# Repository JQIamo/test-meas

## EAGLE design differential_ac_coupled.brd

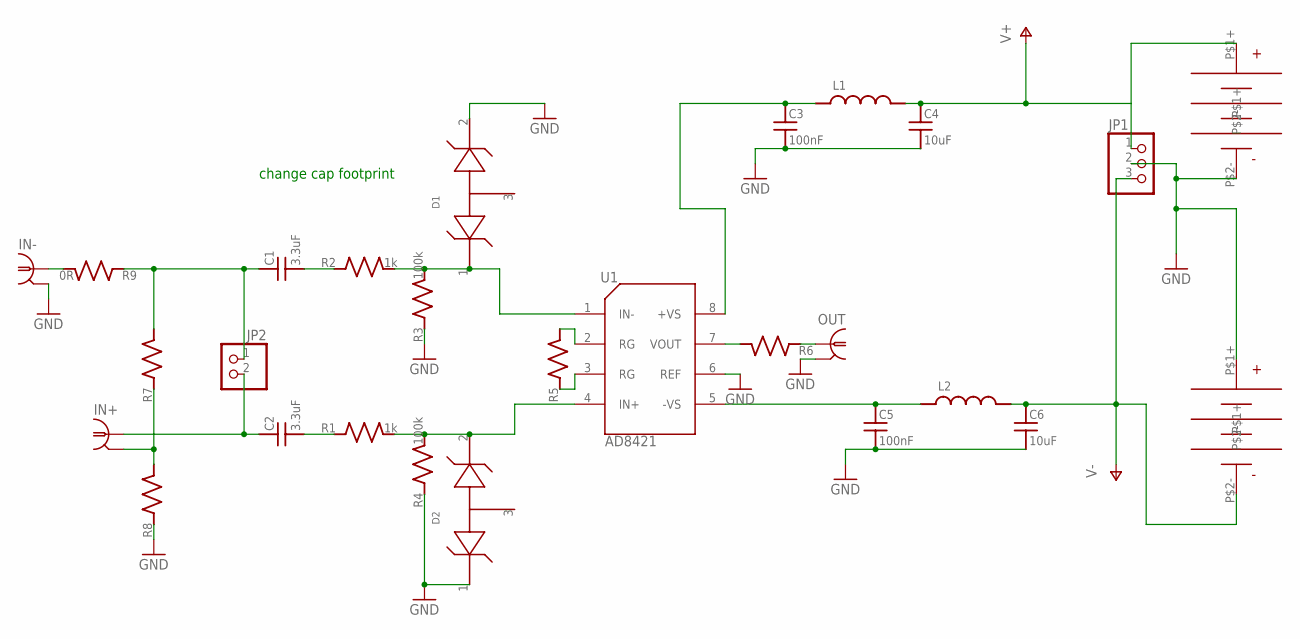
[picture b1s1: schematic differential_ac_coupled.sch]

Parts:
C1, C2: 3.3uF; CKG-JLEAD
C3, C5: 100nF; C_MLCC_0603
C4, C6: 10uF; C_MLCC_0805
D1, D2: ZENER-DUAL; SOT-23
IN+: BNC-H; BNC90
IN-: BNC-H; BNC90
JP1: PINHD-1X3; 1X03
JP2: SCRWTRM-1X2/90_ED550; 1X02_RA_SCRWTRM_ED550
L1, L2: L_FERRITE_SMDLFERRITE_0603; L_FERRITE_0603
OUT: BNC-H; BNC90
R1, R2: 1k; R_1206
R3, R4: 100k; R_1206
R5, R6: R_SMDR0603; R_0603
R7, R8: R_SMDR1206; R_1206
R9: 0R; R_1206
U1: AD8421; SOIC-8
U$1, U$2: BATT-HOLDER; BH23A-BATT-HOLDER

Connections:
GND: C3.P$2 (2), C4.P$2 (2), C5.P$2 (2), C6.P$2 (2), D1.2, D2.1, IN-.2, JP1.2, OUT.2, R3.P$1 (1), R4.P$1 (1), R8.P$1 (1), U1.6 (REF), U$1.P$2-, U$2.P$1+
unnamed: C1.P$2 (2), R2.P$1 (1)
unnamed: C2.P$2 (2), R1.P$1 (1)
unnamed: D2.2, R1.P$2 (2), R4.P$2 (2), U1.4 (IN+)
unnamed: D1.1, R2.P$2 (2), R3.P$2 (2), U1.1 (IN-)
unnamed: OUT.1, R6.P$1 (1)
unnamed: C3.P$1 (1), L1.P$1 (1), U1.8 (+VS)
unnamed: R5.P$2 (2), U1.2 (RG)
unnamed: R5.P$1 (1), U1.3 (RG)
unnamed: C5.P$1 (1), L2.P$1 (1), U1.5 (-VS)
unnamed: R6.P$2 (2), U1.7 (VOUT)
unnamed: C2.P$1 (1), IN+.1, JP2.2
unnamed: C1.P$1 (1), JP2.1, R7.P$2 (2), R9.P$1 (1)
unnamed: IN-.1, R9.P$2 (2)
unnamed: IN+.2, R7.P$1 (1), R8.P$2 (2)
V+: C4.P$1 (1), JP1.1, L1.P$2 (2), U$1.P$1+
V-: C6.P$1 (1), JP1.3, L2.P$2 (2), U$2.P$2-

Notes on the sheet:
change cap footprint

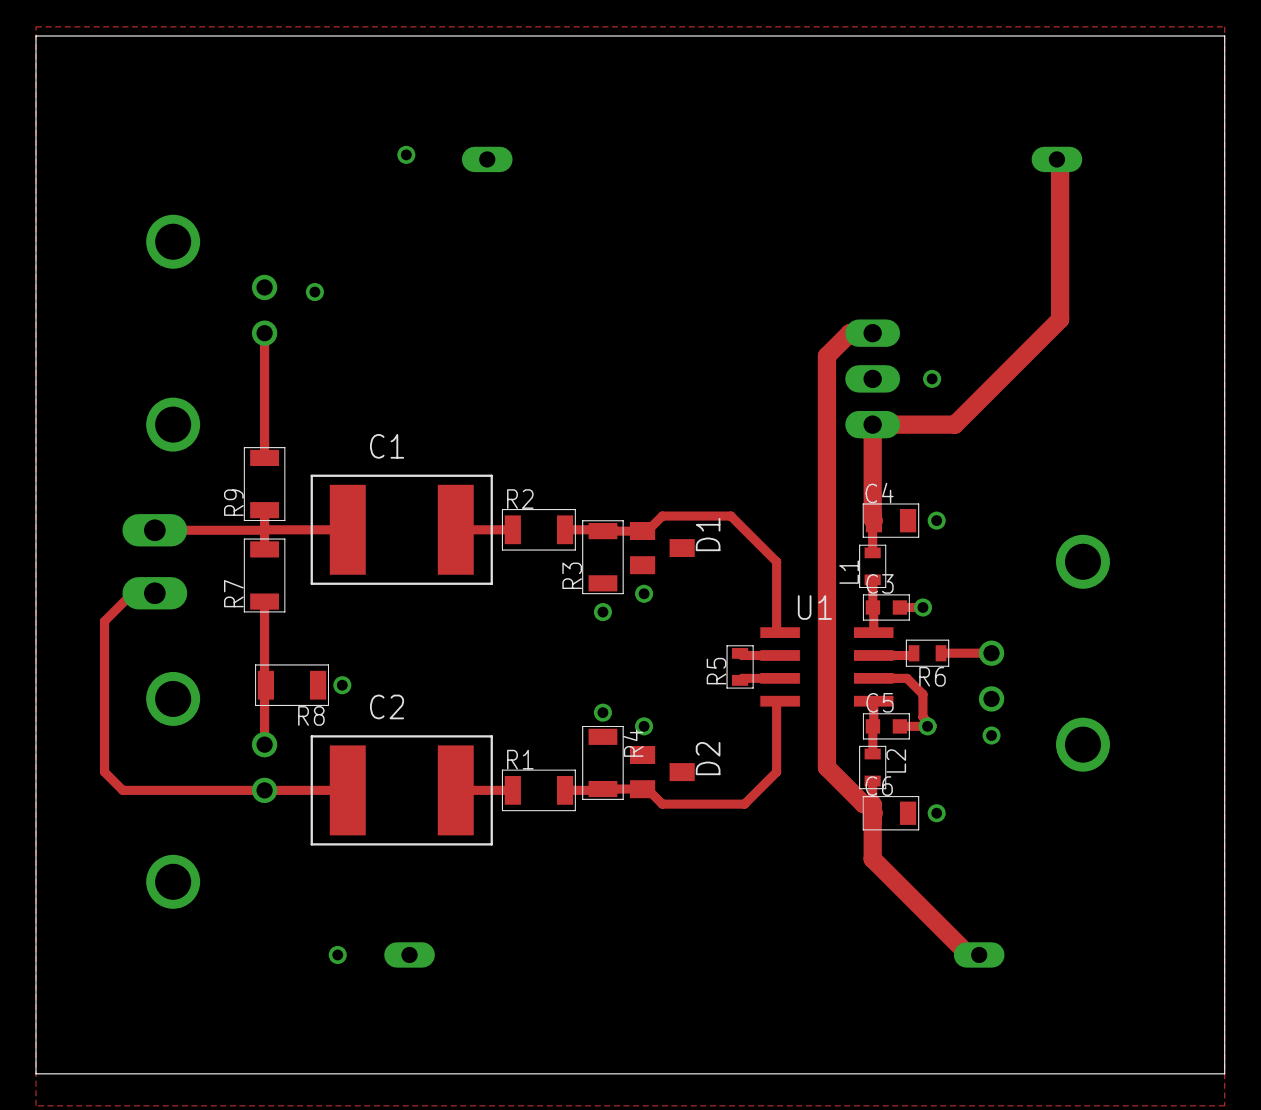
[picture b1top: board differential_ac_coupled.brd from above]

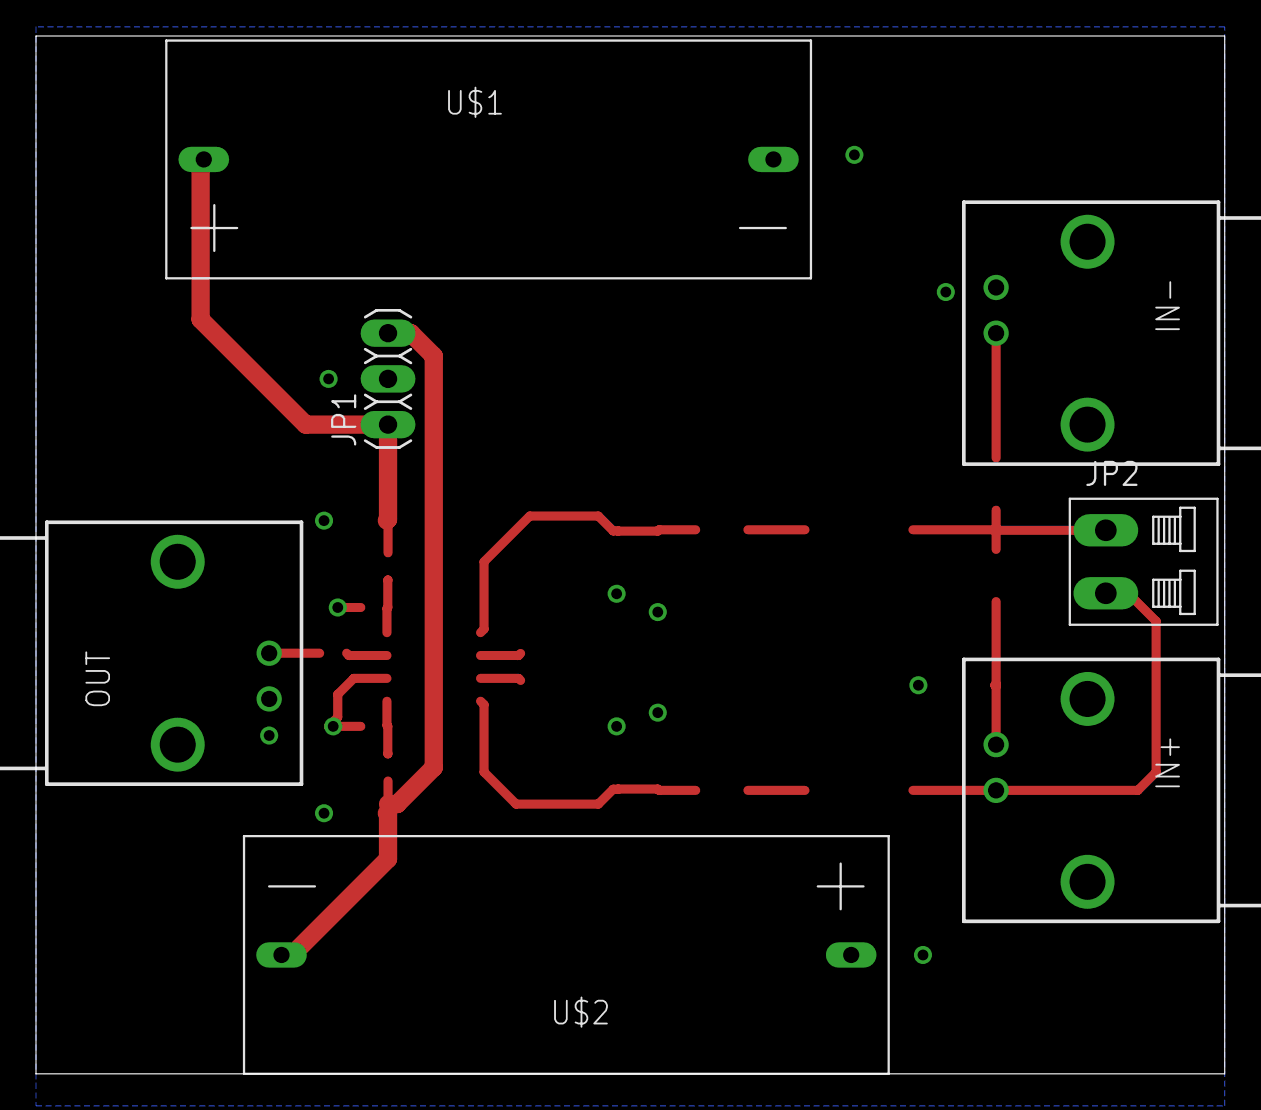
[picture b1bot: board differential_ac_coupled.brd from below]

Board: 2 copper layers, 66.0 x 57.7 mm, 27 parts (7 on the bottom side), 17 nets.

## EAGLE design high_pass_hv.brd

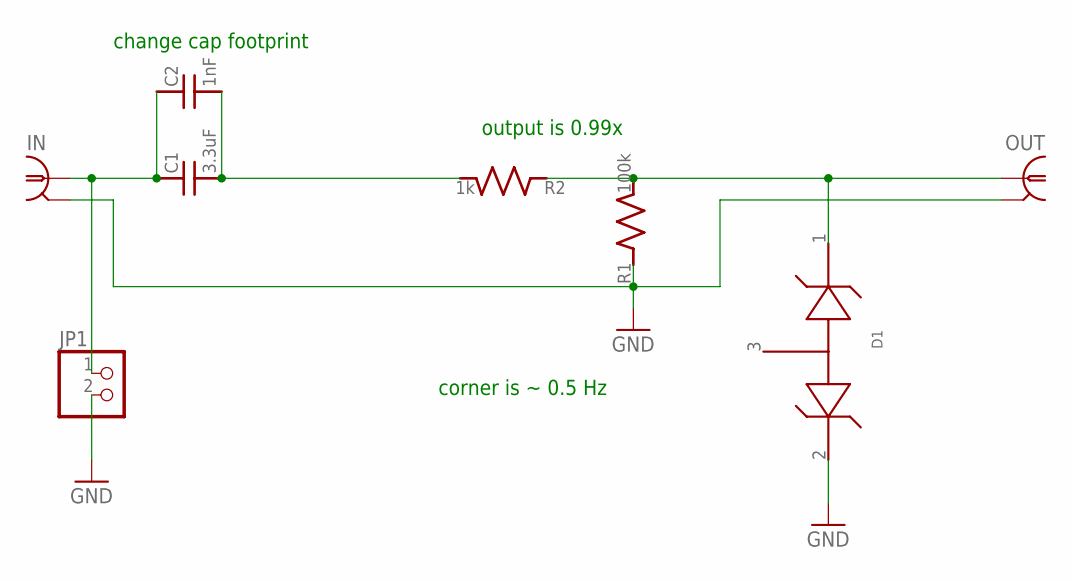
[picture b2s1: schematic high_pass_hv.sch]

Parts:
C1: 3.3uF; CKG-JLEAD
C2: 1nF; C_MLCC_1206
D1: ZENER-DUAL; SOT-23
IN: BNC-H; BNC90
JP1: SCRWTRM-1X2/90_ED550; 1X02_RA_SCRWTRM_ED550
OUT: BNC-H; BNC90
R1: 100k; R_1206
R2: 1k; R_1206

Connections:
GND: D1.2, IN.2, JP1.2, OUT.2, R1.P$1 (1)
unnamed: C1.P$1 (1), C2.P$1 (1), IN.1, JP1.1
unnamed: C1.P$2 (2), C2.P$2 (2), R2.P$2 (2)
unnamed: D1.1, OUT.1, R1.P$2 (2), R2.P$1 (1)

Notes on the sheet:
change cap footprint
output is 0.99x
corner is ~ 0.5 Hz

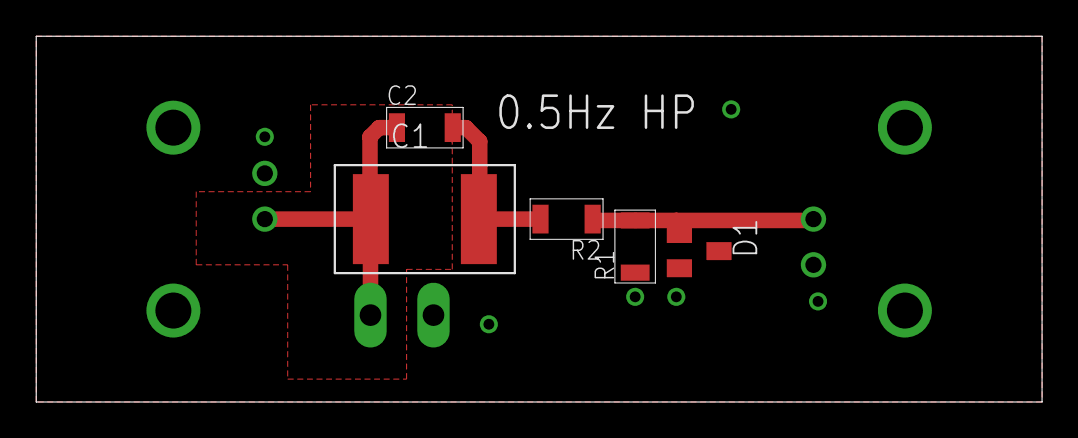
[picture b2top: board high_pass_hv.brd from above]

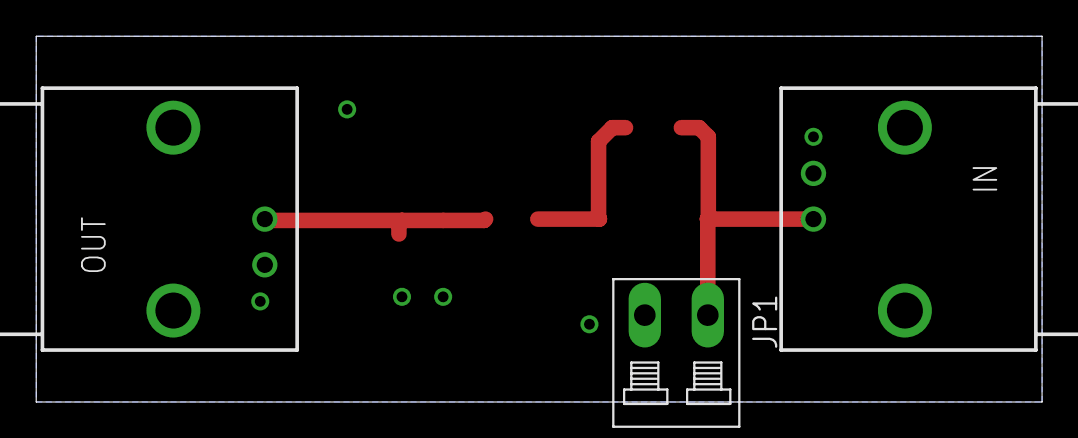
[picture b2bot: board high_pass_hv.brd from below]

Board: 2 copper layers, 55.9 x 20.3 mm, 8 parts (3 on the bottom side), 4 nets.

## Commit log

2016-02-22 added gitignore
2016-02-22 initial commit of design files
2016-02-22 Add battery holders
2016-02-22 to print
2016-02-22 fixed bottom layer isolation; gnd via names
